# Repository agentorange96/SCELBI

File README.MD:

This repository contains design files I used for my SCELBI-8B build that I put together in 2021.

This includes:
- A front panel with engraved text
- A properly sized metal box for the chassis
- An RS232 interface card that is compatible with the original TTY interface box

Further SCELBI Resources:
- [SCELBI Computer Museum](https://www.scelbi.com/)
- [Mike Willegal's Website/Blog (He is the SCELBI Guru)](https://willegal.net/appleii/appleii-first_page.htm)
- [Artem Kalinchuk's Website](https://www.kalinchuk.com/)
- [Artem Kalinchuk's Github Repo](https://github.com/kalinchuk/scelbi/)

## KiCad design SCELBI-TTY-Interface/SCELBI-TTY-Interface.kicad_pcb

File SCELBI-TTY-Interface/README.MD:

This is a [KiCad](https://www.kicad.org/) project. Generated gerber files can be purchased from your choice of PCB manufacturer. I recommend 4PCB for this project as you can order without a solder mask to match the SCELBI aesthetic.

The original schematic comes from Mike Willegal's blog post found [here](https://www.willegal.net/blog/?p=4459) where he creates an RS232 interface. I adapted the design to a SCELBI-style card with the aim to make it look as much like the original TTY card as possible. This card is pin-compatible with the TTY card and should be able to be swapped into a TTY interface box.

**PLEASE NOTE**
- The following design flaws have been fixed, but are as of yet, but have yet to be tested on a physical board:
- Holes for the capacitor and the diode are narrow
- The pinout may not match that of the original TTY interface as intended

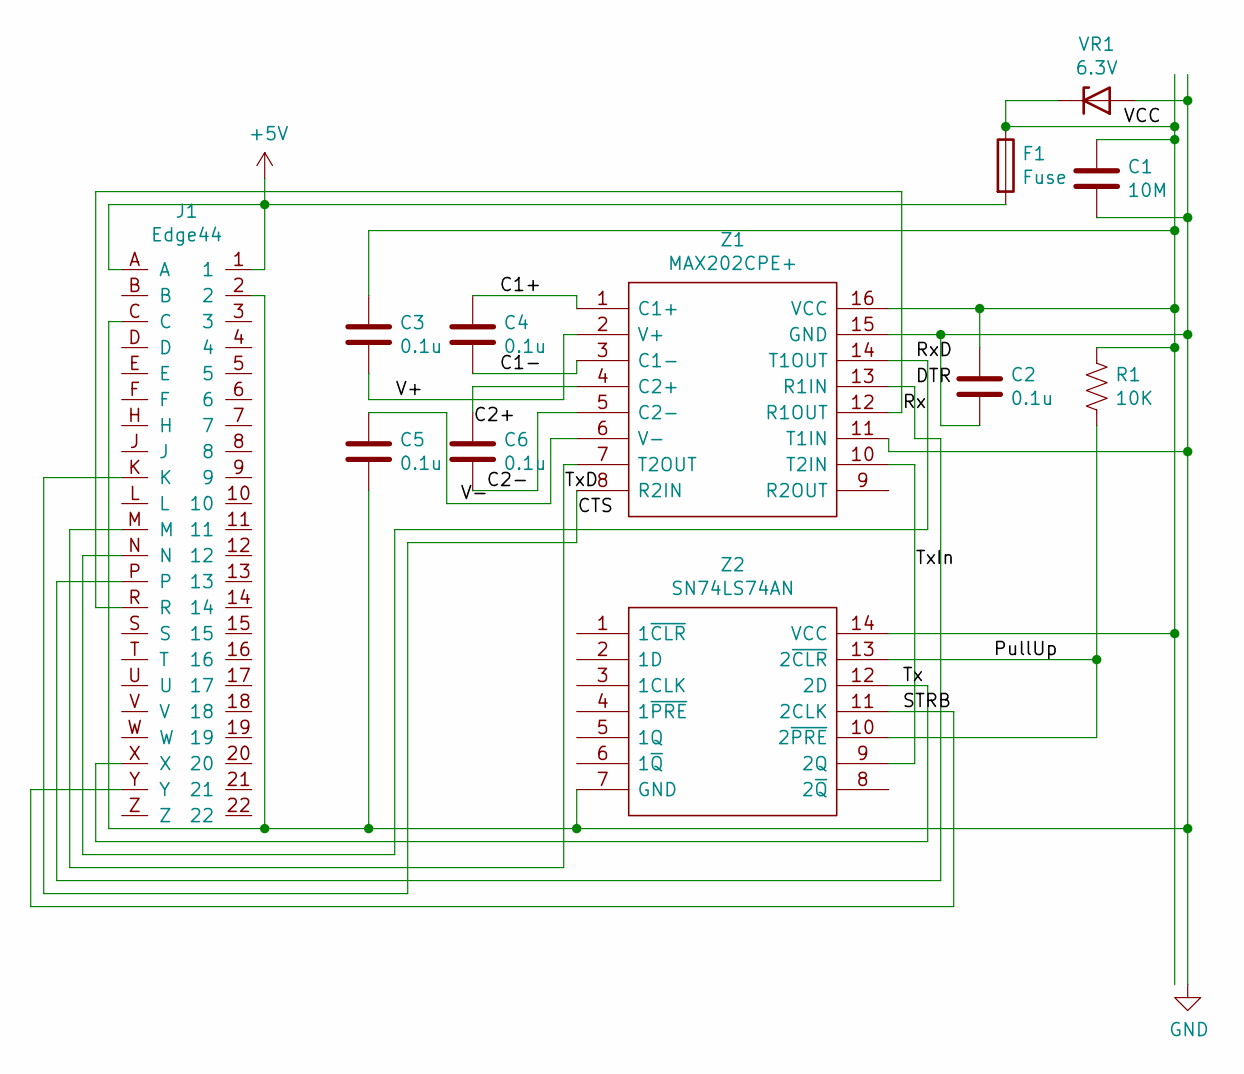
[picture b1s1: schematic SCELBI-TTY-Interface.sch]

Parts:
C1: 10M; C_Axial_L12.0mm_D8.5mm_P20.00mm_Horizontal
C2, C3, C4, C5, C6: 0.1u; C_Disc_D7.5mm_W4.4mm_P6.00mm
F1: Fuse; Fuseholder_AG8
J1: Edge44
R1: 10K; R_Axial_DIN0411_L9.9mm_D3.6mm_P12.70mm_Horizontal
VR1: 6.3V; D_T-1_P12.70mm_Horizontal
Z1: MAX202CPE+; DIP-16_W7.62mm_LongPads; Mouser Part Number 700-MAX202CPE
Z2: SN74LS74AN; DIP-14_W7.62mm_LongPads; Manufacturer_Part_Number SN74LS74AN; Mouser Part Number 595-SN74LS74AN

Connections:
+5V: F1.2, J1.1, J1.A
/C1+: C4.1, Z1.1 (C1+)
/C1-: C4.2, Z1.3 (C1-)
/C2-: C6.2, Z1.5 (C2-)
/DTR: J1.P, Z1.13 (R1IN)
/PullUp: R1.2, Z2.10 (2~PRE), Z2.13 (2~CLR)
/RTS: J1.K, Z1.8 (R2IN)
/Rx: J1.R, Z1.12 (R1OUT)
/RxD: J1.N, Z1.14 (T1OUT)
/STRB: J1.Y, Z2.11 (2CLK)
/Tx: J1.X, Z2.12 (2D)
/TxD: J1.M, Z1.7 (T2OUT)
/TxIn: Z1.10 (T2IN), Z2.9 (2Q)
/V+: C3.2, Z1.2 (V+)
/V-: C5.1, Z1.6 (V-)
/VCC: C1.1, C2.1, C3.1, F1.1, R1.1, VR1.1 (K), Z1.16 (VCC), Z2.14 (VCC)
GND: C1.2, C2.2, C5.2, J1.2, J1.C, VR1.2 (A), Z1.11 (T1IN), Z1.15 (GND), Z2.7 (GND)
unnamed: C6.1, Z1.4 (C2+)

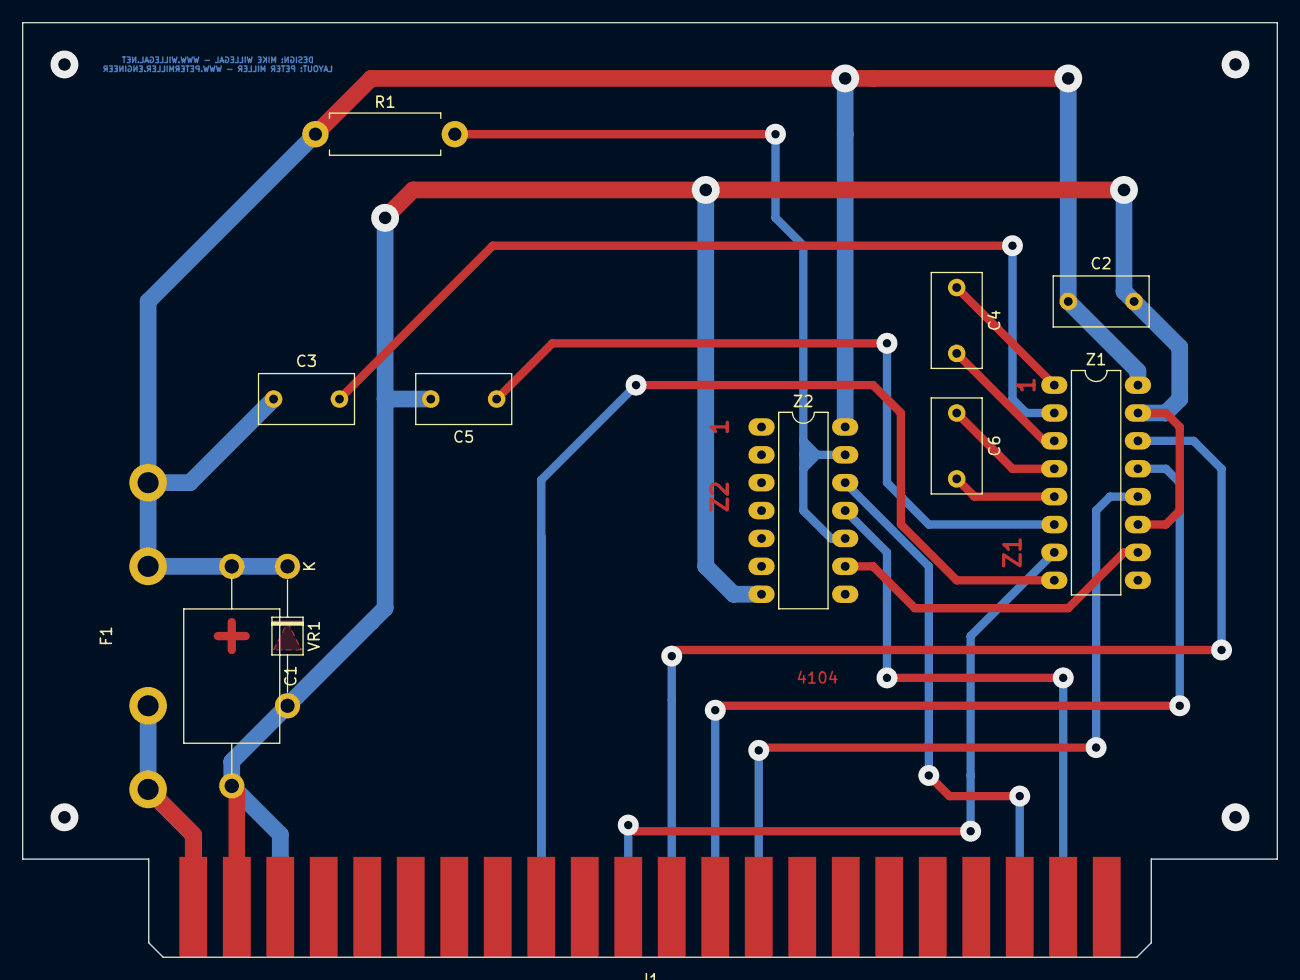
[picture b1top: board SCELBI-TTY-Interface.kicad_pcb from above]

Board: 2 copper layers, 114.3 x 85.1 mm, 12 parts (0 on the bottom side), 18 nets.

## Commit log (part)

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2025-05-16 Update readmes
2025-08-10 Swap out TTY interface project for KiCad project
2025-08-10 Swap strobe/tx, widen drill for supply components, relabel control signals
2025-12-10 Add FSK-Encoder
2025-12-11 Update FSK Encoder to match real SCELBI format
2025-12-11 Brute force timings to match real file
2025-12-11 Added checksum function and example files
